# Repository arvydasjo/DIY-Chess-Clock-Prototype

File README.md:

A personal project for a DIY chess clock. This project includes PCB designs, 3D-printable case files, and firmware for a functional chess clock.

## Features
- Custom PCB with microcontroller STM32F030C8 and screen Grove-LCD 
- 3D-printable case
- small magnets used for the user switch button
- firmware for timing and game management
- Battery-powered

## Files Included
- **PCB/**: Schematic and layout files
- **3D/**: STL files for 3D printing the case
- **Images/**: Prototype pictures
- **Firmware/**: Source code for the microcontroller

## Tools used in the project

- Kicad for PCB design
- STM32CubeIDE + STLINK-V3MINIE for programming, HAL libraries
- Autodesk Fusion for 3D design

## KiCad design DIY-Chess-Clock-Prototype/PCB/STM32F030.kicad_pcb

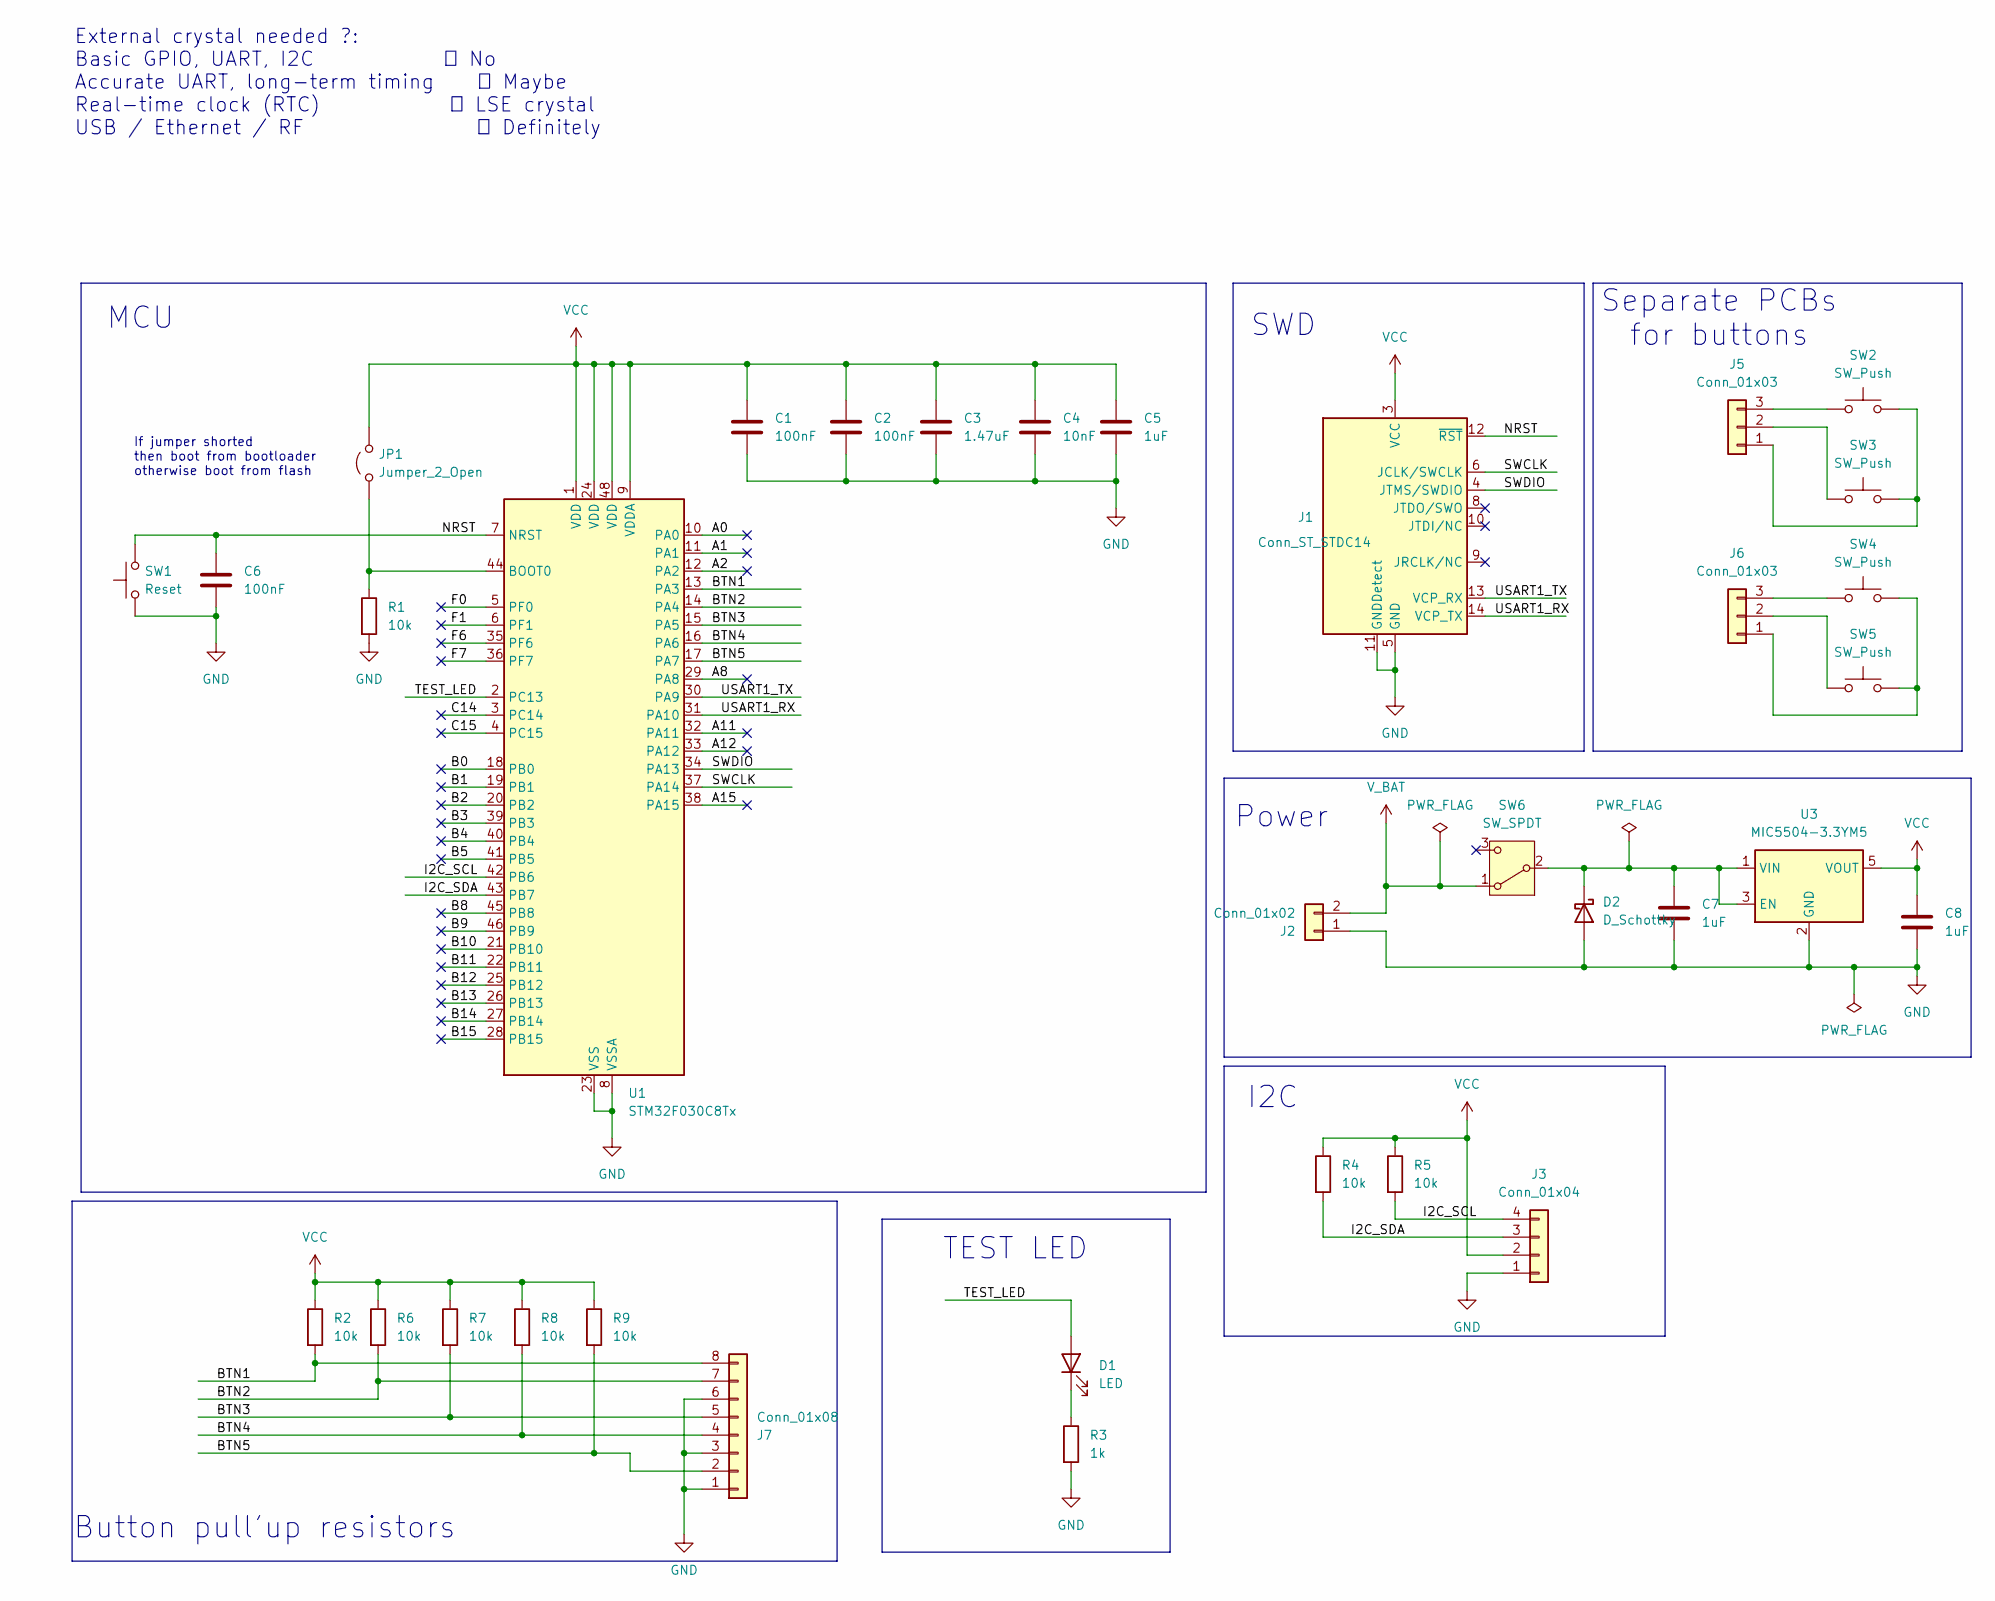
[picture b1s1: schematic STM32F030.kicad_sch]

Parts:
C1, C2, C6: 100nF; C_0603_1608Metric
C3: 1.47uF; C_0603_1608Metric
C4: 10nF; C_0603_1608Metric
C5, C7, C8: 1uF; C_0603_1608Metric
D1: LED; LED_0603_1608Metric
D2: D_Schottky; D_SOD-123
J1: Conn_ST_STDC14; CONN14_3221-14-0300-00-TR_CNC
J2: Conn_01x02; PinHeader_1x02_P2.54mm_Vertical
J3: Conn_01x04; CONN_S4B-PH-K-S_JST
J5, J6: Conn_01x03; PinHeader_1x03_P2.54mm_Vertical
J7: Conn_01x08; PinHeader_1x08_P2.54mm_Vertical
JP1: Jumper_2_Open; SolderJumper-2_P1.3mm_Open_Pad1.0x1.5mm
R1, R2, R4, R5, R6, R7, R8, R9: 10k; R_0603_1608Metric
R3: 1k; R_0603_1608Metric
SW1: Reset; SW_SPST_CK_RS282G05A3
SW2, SW3, SW4, SW5: SW_Push; SW_PUSH-12mm
SW6: SW_SPDT; PinHeader_1x03_P2.54mm_Vertical
U1: STM32F030C8Tx; LQFP-48_7x7mm_P0.5mm
U3: MIC5504-3.3YM5; SOT-23-5

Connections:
/A0: U1.10 (PA0)
/A1: U1.11 (PA1)
/A2: U1.12 (PA2)
/A8: U1.29 (PA8)
/A11: U1.32 (PA11)
/A12: U1.33 (PA12)
/A15: U1.38 (PA15)
/B0: U1.18 (PB0)
/B1: U1.19 (PB1)
/B2: U1.20 (PB2)
/B3: U1.39 (PB3)
/B4: U1.40 (PB4)
/B5: U1.41 (PB5)
/B8: U1.45 (PB8)
/B9: U1.46 (PB9)
/B10: U1.21 (PB10)
/B11: U1.22 (PB11)
/B12: U1.25 (PB12)
/B13: U1.26 (PB13)
/B14: U1.27 (PB14)
/B15: U1.28 (PB15)
/BTN1: J7.8, R2.2, U1.13 (PA3)
/BTN2: J7.7, R6.2, U1.14 (PA4)
/BTN3: J7.5, R7.2, U1.15 (PA5)
/BTN4: J7.4, R8.2, U1.16 (PA6)
/BTN5: J7.2, R9.2, U1.17 (PA7)
/C14: U1.3 (PC14)
/C15: U1.4 (PC15)
/F0: U1.5 (PF0)
/F1: U1.6 (PF1)
/F6: U1.35 (PF6)
/F7: U1.36 (PF7)
/I2C_SCL: J3.4, R5.2, U1.42 (PB6)
/I2C_SDA: J3.3, R4.2, U1.43 (PB7)
/NRST: C6.1, J1.12 (~RST), SW1.2, U1.7 (NRST)
/SWCLK: J1.6 (JCLK/SWCLK), U1.37 (PA14)
/SWDIO: J1.4 (JTMS/SWDIO), U1.34 (PA13)
/TEST_LED: D1.2 (A), U1.2 (PC13)
/USART1_RX: J1.14 (VCP_TX), U1.31 (PA10)
/USART1_TX: J1.13 (VCP_RX), U1.30 (PA9)
GND: C1.2, C2.2, C3.2, C4.2, C5.2, C6.2, C7.2, C8.2, D2.2 (A), J1.5 (GND), J1.7 (GND), J1.11 (GNDDetect), J2.1, J3.1, J7.1, J7.3, J7.6, R1.2, R3.2, SW1.1, U1.8 (VSSA), U1.23 (VSS), U1.47 (VSS), U3.2 (GND)
unnamed: D1.1 (K), R3.1
unnamed: C7.1, D2.1 (K), SW6.2 (B), U3.1 (VIN), U3.3 (EN)
unnamed: J5.1, SW2.2, SW3.2
unnamed: J5.2, SW3.1
unnamed: J5.3, SW2.1
unnamed: J6.1, SW4.2, SW5.2
unnamed: J6.2, SW5.1
unnamed: J6.3, SW4.1
unnamed: JP1.1 (A), R1.1, U1.44 (BOOT0)
VCC: C1.1, C2.1, C3.1, C4.1, C5.1, C8.1, J1.3 (VCC), J3.2, JP1.2 (B), R2.1, R4.1, R5.1, R6.1, R7.1, R8.1, R9.1, U1.1 (VDD), U1.9 (VDDA), U1.24 (VDD), U1.48 (VDD), U3.5 (VOUT)
V_BAT: J2.2, SW6.1 (A)

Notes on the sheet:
MCU
Button pull'up resistors
Power
If jumper shorted then boot from bootloader otherwise boot from flash
External crystal needed ?: Basic GPIO, UART, I2C ❌ No Accurate UART, long-term timing ✅ Maybe Real-time clock (RTC) ✅ LSE crystal USB / Ethernet / RF ✅ Definitely
SWD
TEST LED
I2C
Separate PCBs for buttons

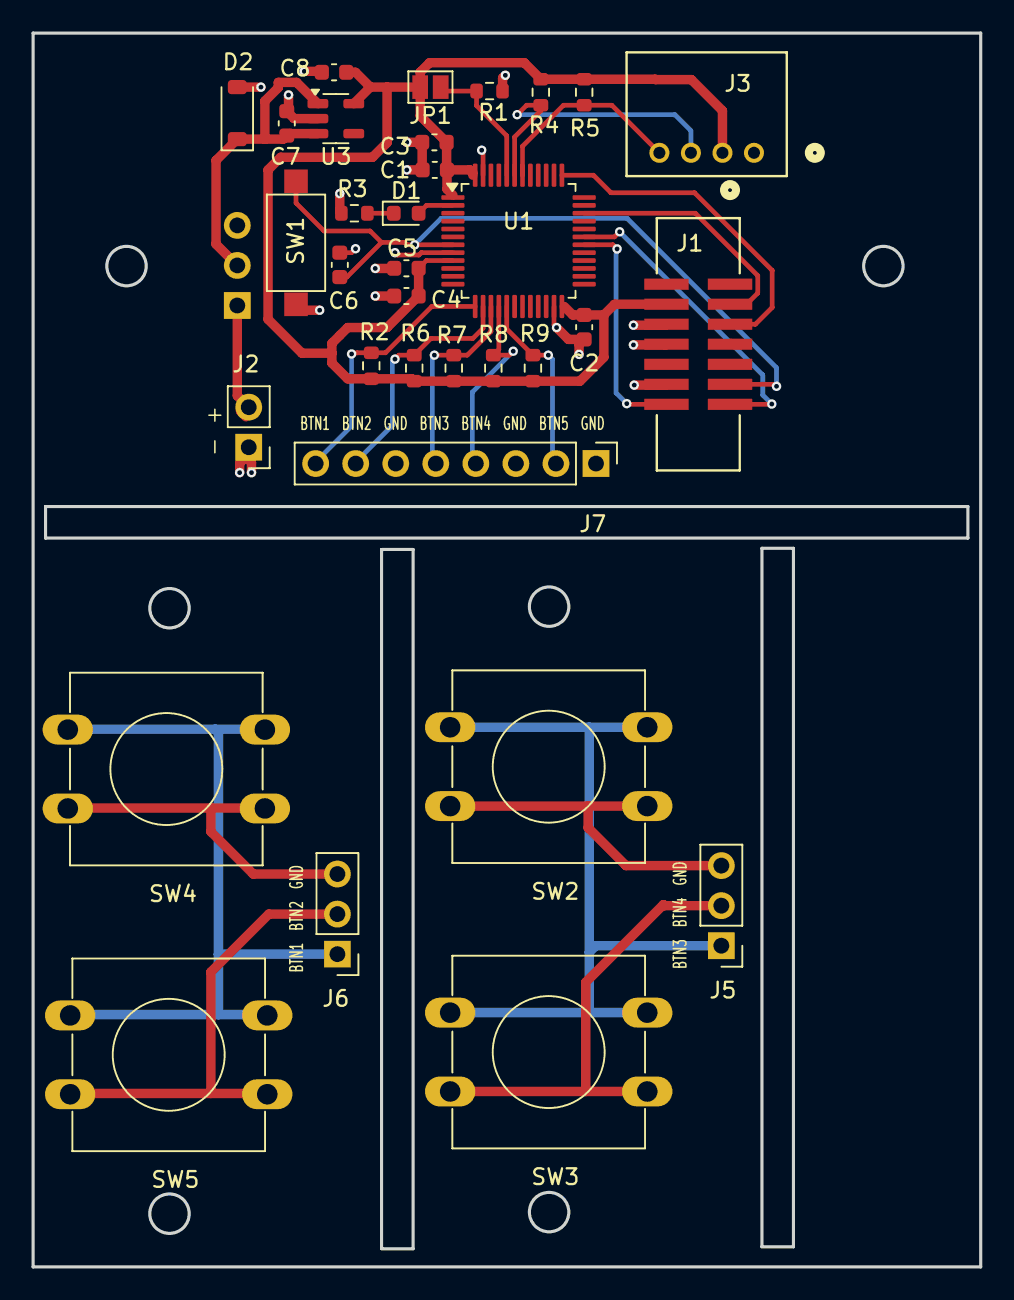
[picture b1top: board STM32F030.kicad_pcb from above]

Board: 2 copper layers, 60.1 x 78.2 mm, 34 parts (1 on the bottom side), 25 nets.

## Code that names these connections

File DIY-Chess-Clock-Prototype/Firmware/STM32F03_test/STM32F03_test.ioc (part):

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Mcu.Name=STM32F030C8Tx
Mcu.Package=LQFP48
Mcu.UserName=STM32F030C8Tx
PA13.Mode=Serial_Wire
PA13.Signal=SYS_SWDIO
PA14.Mode=Serial_Wire
PA14.Signal=SYS_SWCLK
PA3.GPIOParameters=GPIO_ModeDefaultEXTI
PA3.GPIO_ModeDefaultEXTI=GPIO_MODE_IT_FALLING
PA3.Signal=GPXTI3
PA4.GPIOParameters=GPIO_ModeDefaultEXTI
PA4.GPIO_ModeDefaultEXTI=GPIO_MODE_IT_FALLING
PA4.Signal=GPXTI4
PA5.GPIOParameters=GPIO_PuPd,GPIO_ModeDefaultEXTI
PA5.GPIO_ModeDefaultEXTI=GPIO_MODE_IT_FALLING
PA5.GPIO_PuPd=GPIO_NOPULL
PA5.Signal=GPXTI5
PA6.GPIOParameters=GPIO_PuPd,GPIO_ModeDefaultEXTI
PA6.GPIO_ModeDefaultEXTI=GPIO_MODE_IT_FALLING
PA6.GPIO_PuPd=GPIO_NOPULL
PA6.Signal=GPXTI6
PA7.GPIOParameters=GPIO_PuPd,GPIO_ModeDefaultEXTI
PA7.GPIO_ModeDefaultEXTI=GPIO_MODE_IT_RISING_FALLING
PA7.GPIO_PuPd=GPIO_NOPULL
PA7.Signal=GPXTI7
PB6.GPIOParameters=GPIO_Pu
PB6.GPIO_Pu=GPIO_PULLUP
PB6.Mode=I2C
PB6.Signal=I2C1_SCL
PB7.GPIOParameters=GPIO_Pu
PB7.GPIO_Pu=GPIO_PULLUP
PB7.Mode=I2C
PB7.Signal=I2C1_SDA
PC13.Signal=GPIO_Output
board=custom

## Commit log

2025-10-07 Create Firmware
2026-04-21 Created using Colab
